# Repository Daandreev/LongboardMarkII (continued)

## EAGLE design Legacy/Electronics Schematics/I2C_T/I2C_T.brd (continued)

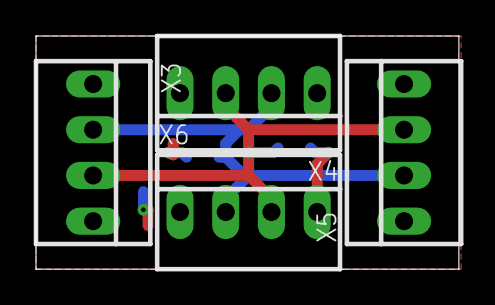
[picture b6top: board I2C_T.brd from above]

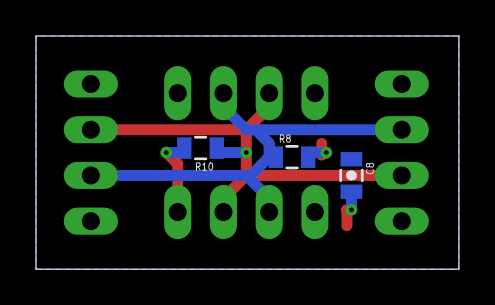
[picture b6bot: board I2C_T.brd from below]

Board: 2 copper layers, 23.5 x 13.0 mm, 7 parts (3 on the bottom side), 4 nets.

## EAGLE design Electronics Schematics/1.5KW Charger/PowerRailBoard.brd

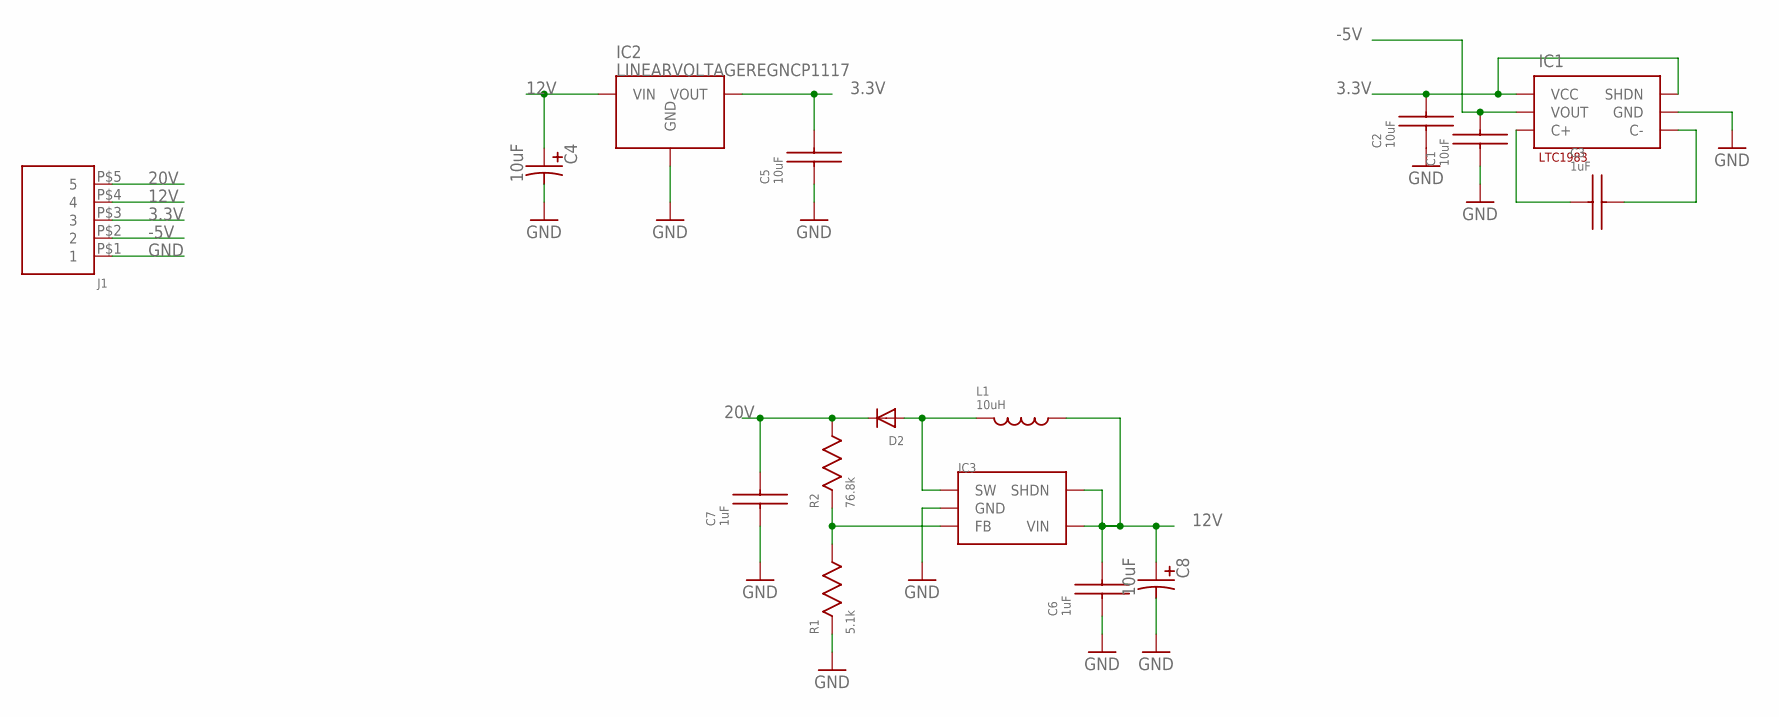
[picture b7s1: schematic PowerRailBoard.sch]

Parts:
C1, C2, C5: 10uF; 0805_(2012_METRIC)
C3, C6, C7: 1uF; 0805_(2012_METRIC)
C4, C8: 10uF; CAP_SSER_5MMX5MM
D2: DIODESOD-123; SOD-123
IC1: LTC1983; TSOT23-6
IC2: LINEARVOLTAGEREGNCP1117; DPAK
IC3: AP301; SOT-23
J1: CONNECTOR_5PIN; 5PIN_.1'
L1: 10uH; 0805_(2012_METRIC)
R1: 5.1k; 0805_(2012_METRIC)
R2: 76.8k; 0805_(2012_METRIC)

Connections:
3.3V: C2.P$1, C5.P$1, IC1.1 (VCC), IC1.6 (SHDN), IC2.2 (VOUT), J1.P$3 (3)
12V: C4.P (POSITIVE), C6.P$1, C8.P (POSITIVE), IC2.3 (VIN), IC3.4 (SHDN), IC3.5 (VIN), J1.P$4 (4), L1.P$2
20V: C7.P$1, D2.C, J1.P$5 (5), R2.P$1
-5V: C1.P$1, IC1.2 (VOUT), J1.P$2 (2)
GND: C1.P$2, C2.P$2, C4.N (NEGATIVE), C5.P$2, C6.P$2, C7.P$2, C8.N (NEGATIVE), IC1.5 (GND), IC2.1 (GND), IC3.2 (GND), J1.P$1 (1), R1.P$2
unnamed: C3.P$2, IC1.3 (C+)
unnamed: C3.P$1, IC1.4 (C-)
unnamed: D2.A, IC3.1 (SW), L1.P$1
unnamed: IC3.3 (FB), R1.P$1, R2.P$2

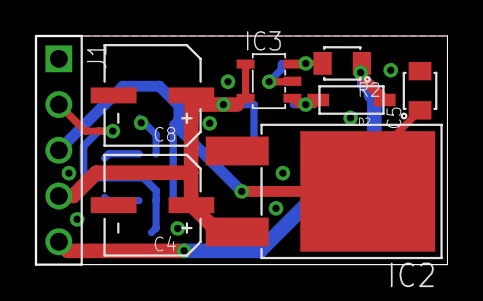
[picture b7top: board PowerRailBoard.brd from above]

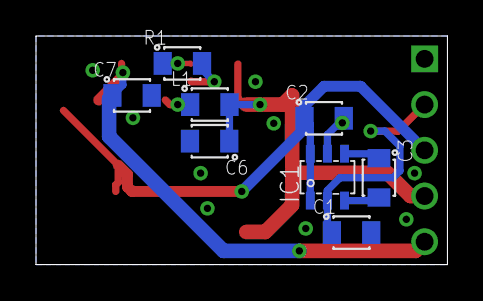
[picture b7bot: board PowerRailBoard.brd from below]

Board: 2 copper layers, 22.9 x 12.7 mm, 16 parts (8 on the bottom side), 9 nets.

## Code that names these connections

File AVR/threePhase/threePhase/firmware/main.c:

#include <avr/io.h>
#include <util/delay.h>

#define phaseAL PB0
#define phaseBL PB1
#define phaseCL PB2

#define phaseAH PB3
#define phaseBH PB4
#define phaseCH PB5


void timer0_init(int prescaler)
{
    if(prescaler==1)                    //clk/1
    {
        TCCR0 |= (1 << CS00);
    }
    if(prescaler==8)                    //clk/8
    {
        TCCR0 |= (1 << CS01);
    }
    if(prescaler==64)                    //clk/64
    {
        TCCR0 |= (1 << CS00)|(1<<CS01);
    }
    if(prescaler==256)                    //clk/256
    {
        TCCR0 |= (1<<CS02);
    }
    if(prescaler==1024)                    //clk/1024
    {
        TCCR0 |= (1 << CS00)|(1<<CS02);
    }
}

void timer1_init(int prescaler)
{
    if(prescaler==1)                    //clk/1
    {
        TCCR1B |= (1 << CS10);
    }
    if(prescaler==8)                    //clk/8
    {
        TCCR1B |= (1 << CS11);
    }
    if(prescaler==64)                    //clk/64
    {
        TCCR1B |= (1 << CS10)|(1<<CS11);
    }
    if(prescaler==256)                    //clk/256
    {
        TCCR1B |= (1<<CS12);
    }
    if(prescaler==1024)                    //clk/1024
    {
        TCCR1B |= (1 << CS10)|(1<<CS12);
    }
}

void timer2_init(int prescaler)
{
    if(prescaler==1)                    //clk/1
    {
        TCCR2 |= (1 << CS20);
    }
    if(prescaler==8)                    //clk/8
    {
        TCCR2 |= (1 << CS21);
    }
    if(prescaler==32)                    //clk/32
    {
        TCCR2 |= (1 << CS21)|(1<<CS20);
    }
    if(prescaler==64)                    //clk/64
    {
        TCCR2 |= (1 << CS22);
    }
    if(prescaler==128)                    //clk/128
    {
        TCCR2 |= (1<<CS22)|(1<<CS20);
    }
    if(prescaler==256)                    //clk/256
    {
        TCCR2 |= (1 << CS22)|(1<<CS21);
    }
    if(prescaler==1024)                    //clk/1024
    {
        TCCR2 |= (1 << CS22)|(1<<CS21)|(1<<CS20);
    }
}

void phaseFire(int phase, int condition)
{
    if(phase == 1) //PhaseAH
    {
        if(condition==1)
        {
            PORTD |= (1<<phaseAH);
        }
        else
        {
            PORTD &= ~(1<<phaseAH);
        }
    }
    if(phase == 2) //PhaseBH
    {
        if(condition==1)
        {
            PORTD |= (1<<phaseBH);
        }
        else
        {
            PORTD &= ~(1<<phaseBH);
        }
    }
    if(phase == 3) //PhaseCH
    {
        if(condition==1)
        {
            PORTD |= (1<<phaseCH);
        }
        else
        {
            PORTD &= ~(1<<phaseCH);
        }
    }
    if(phase == 4) //PhaseAL
    {
        if(condition==1)
        {
            PORTD |= (1<<phaseAL);
        }
        else
        {
            PORTD &= ~(1<<phaseAL);
        }
    }
    if(phase == 5) //PhaseBL
    {
        if(condition==1)
        {
            PORTD |= (1<<phaseBL);
        }
        else
        {
            PORTD &= ~(1<<phaseBL);
        }
    }
    if(phase == 6) //PhaseCL
    {
        if(condition==1)
        {
            PORTD |= (1<<phaseCL);
        }
        else
        {
            PORTD &= ~(1<<phaseCL);
        }
    }
}

void cycle(int phase, int duty, int duration)
{
// (A/B/C,0-255,(ms))
//pass which phase, duration, and the duty cycle at which to perform a single cycle
    if(phase==1)//PhaseAH
    {
        
        phaseFire(2,0); //Set PhaseBH Low
        phaseFire(3,0); //Set PhaseCH Low
        phaseFire(5,1); //Set PhaseBL High
        phaseFire(6,1); //Set PhaseCL High
        
        phaseFire(4,0); //Set PhaseAL Low
        
        timer0_init(1024);//timer 0 measures duration of entire cycle
        timer2_init(1);//timer 1 measures duty cycles
        TCNT0 = 0;
        TCNT2 = 0;

        while(TCNT0<=duration)
        {
            if(TCNT2<duty)
            {
                phaseFire(1,1);
            }
            else
            {
                phaseFire(1,0);
            }
        }
        phaseFire(1,0);
        return;
    }
    if(phase==2)//PhaseBH
    {
        
        phaseFire(1,0); //Set PhaseAH Low
        phaseFire(3,0); //Set PhaseCH Low
        phaseFire(4,1); //Set PhaseAL High
        phaseFire(6,1); //Set PhaseCL High
        
        phaseFire(5,0); //Set PhaseBL Low
        
        timer0_init(1024);//timer 0 measures duration of entire cycle
        timer2_init(1);//timer 1 measures duty cycles
        TCNT0 = 0;
        TCNT2 = 0;
        while(TCNT0<=duration)
        {
            if(TCNT2<duty)
            {
                phaseFire(2,1);
            }
            else
            {
                phaseFire(2,0);
            }
        }
        phaseFire(2,0);
        return;
    }
    if(phase==3)//PhaseCH
    {
        
        phaseFire(1,0); //Set PhaseAH Low
        phaseFire(2,0); //Set PhaseBH Low
        phaseFire(4,1); //Set PhaseAL High
        phaseFire(5,1); //Set PhaseBL High
        
        phaseFire(6,0); //Set PhaseCL Low
       
        timer0_init(1024);//timer 0 measures duration of entire cycle
        timer2_init(1);//timer 1 measures duty cycles
        TCNT0 = 0;
        TCNT2 = 0;
        while(TCNT0<=duration)
        {
            if(TCNT2<duty)
            {
                phaseFire(3,1);
            }
            else
            {
                phaseFire(3,0);
            }
            
        }
        phaseFire(3,0);
        return;
    }
}

void fade(int duty, int duration)
{
    for (duty = 1; duty < 255; ++duty)
    {
        phaseFire(2,0);
        phaseFire(3,0);
        cycle(1,duty,duration);
        phaseFire(1,0);
        
        phaseFire(1,0);
        phaseFire(3,0);
        cycle(2,duty,duration);
        phaseFire(2,0);
        
        phaseFire(1,0);
        phaseFire(2,0);
        cycle(3,duty,duration);
        phaseFire(3,0);
    }
    for (duty = 255; duty > 1; --duty)
    {
        
        phaseFire(2,0);
        phaseFire(3,0);
        cycle(1,duty,duration);
        phaseFire(1,0);
        
        phaseFire(1,0);
        phaseFire(3,0);
        cycle(2,duty,duration);
        phaseFire(2,0);
        
        phaseFire(1,0);
        phaseFire(2,0);
        cycle(3,duty,duration);
        phaseFire(3,0);
    }
}

void degreeFire(int degree)
{
    if(degree <= 60)
        //A Increasing
        //B Zero
        //C Max
    {
        phaseFire(2,0);
        phaseFire(3,1);
        
    }
    
    if(degree <= 120)
        //A Max
        //B Zero
        //C Decreasing
    {
        
    }
    
    if(degree <= 180)
        //A Max
        //B Increasing
        //C Zero
    {
        
    }
    
    if(degree <= 240)
        //A Decreasing
        //B Max
        //C Zero
    {
        
    }
    
    if(degree <= 300)
        //A Zero
        //B Max
        //C Increasing
    {
        
    }
    
    if(degree <= 360)
        //A Zero
        //B Decreasing
        //C Max
    {
        
    }
}

int main(void)
{
    DDRD |= (1 << phaseAH);
    DDRD |= (1 << phaseBH);
    DDRD |= (1 << phaseCH);
    DDRD |= (1 << phaseAL);
    DDRD |= (1 << phaseBL);
    DDRD |= (1 << phaseCL);
    int duty = 40;
    int duration = 50;                    // make sure duration can never be larger than 2
    int i;
    int ramp = 5;
    
    while(1)
    {
        for(i=10;i<20;i++)
        {
        cycle(1,i,ramp);
        }
        cycle(1,duty,duration);
        for(i=20;i>10;i--)
        {
        cycle(1,i,ramp);
        }
        
        
        for(i=10;i<20;i++)
        {
            cycle(2,i,ramp);
        }
        cycle(2,duty,duration);
        for(i=20;i>10;i--)
        {
            cycle(2,i,ramp);
        }
        
        
        for(i=10;i<20;i++)
        {
            cycle(3,i,ramp);
        }
        cycle(3,duty,duration);
        for(i=20;i>10;i--)
        {
            cycle(3,i,ramp);
        }
       // cycle(2,duty,duration);
        //cycle(3,duty,duration);
        /*
        for(i = 240; i>60;i--)
        {
        cycle(1,duty,i);
        cycle(2,duty,i+1);
        cycle(3,duty,i+2);
        }
        for(i = 60; i<240 ;i++)
        {
            cycle(1,duty,i);
            cycle(2,duty,i+1);
            cycle(3,duty,i+2);
        }
         */

    }
    return 0;
}

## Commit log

2017-08-15 added MarkII project
2017-08-16 established symmetry of board (V5)
2017-08-16 deck symmetry attained, tubular battery holders made
2017-08-16 untracked files added
2017-08-17 batterypackholders created
2017-08-17 tubular batterypack expanded to hold 64 cells, spring compression fitting
2017-08-17 routed each cell, no issues in tubular battery pack assembly
2017-08-17 Final Assembly V8 Created, includes powerpack subassembly
2017-08-17 pack connectors are now an assembly
2017-08-18 Deck Redesign 9th itiration of the final assembly
2017-08-18 Deck Edges Chambfered
2017-08-18 fixed minor assembly errors in assembly
2017-08-18 photos added, ReadMe updated
2017-08-18 README test
2017-08-19 README v2
2017-08-19 Extra Picture(s)
2017-08-20 Organized the mess a bit
2017-08-20 Added SlideStrut
2017-08-21 grind strut++
2017-08-22 Terrain collsision test round 1
2017-08-28 removed video
2017-08-28 EndCap assmble for Tubular Packs
2017-08-30 board v6 molding
2017-08-30 fixed tub pack assembly errors and started press
2017-08-30 added tubular pack endcap pcb
2017-09-01 Started BOM
2017-09-03 BOM, Spacer, Bumper draft
2017-09-07 grind rail updated
2017-09-08 Grindbridge adjust + BOM + hardware inclusion beggining
2017-09-10 fasteners folder, BOM for battery pack
2017-09-10 Compiled Bat Holder BOM
2017-09-16 CNC cam file start, BOM update
2017-09-20 grind rails and updated bat holder assembly
2017-09-22 grind rail CNC CAM work
2017-10-01 Renders for project log
2017-10-01 added EV sensor module
2017-10-01 EV module full assembly
2017-10-02 EV module final assembly update
2017-10-03 Mold update and redo
2017-10-03 Mold Flat Finished
2017-10-04 battery spacer and contact re-designed
2017-10-16 Battery connector updated, GPS Module enclosure made
2017-10-17 Exploded view, Project Porfolio
2017-11-07 touchups, mainly working in hardware atm
2017-11-08 BOM update
2017-11-15 battery spacer
2017-11-24 Electronics start, GPS code
2017-11-27 GPS data conversion, google api working
2018-01-04 resume update
2018-01-28 BMS MAX14921 Board Rev 1
2018-01-31 connector PCBs and such
2018-02-01 dank work bean
2018-02-01 dual pcb layer connector
2018-02-04 cleaned up files, created legacy folders
2018-02-05 redesigned PCBEndCap to include GND and VCC
2018-02-05 front pcbconnector redesigned
2018-02-06 vesc and backend connectors adjusted
2018-02-11 pcb spacer and breakoutoard over
2018-02-26 updated Max14921 Breakout Board
